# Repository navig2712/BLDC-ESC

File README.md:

# BLDC-ESC
All the files necessary files include  code for  DIY BLDC ESC
ESC V0----PCB files
Protues---Simulation files
Code

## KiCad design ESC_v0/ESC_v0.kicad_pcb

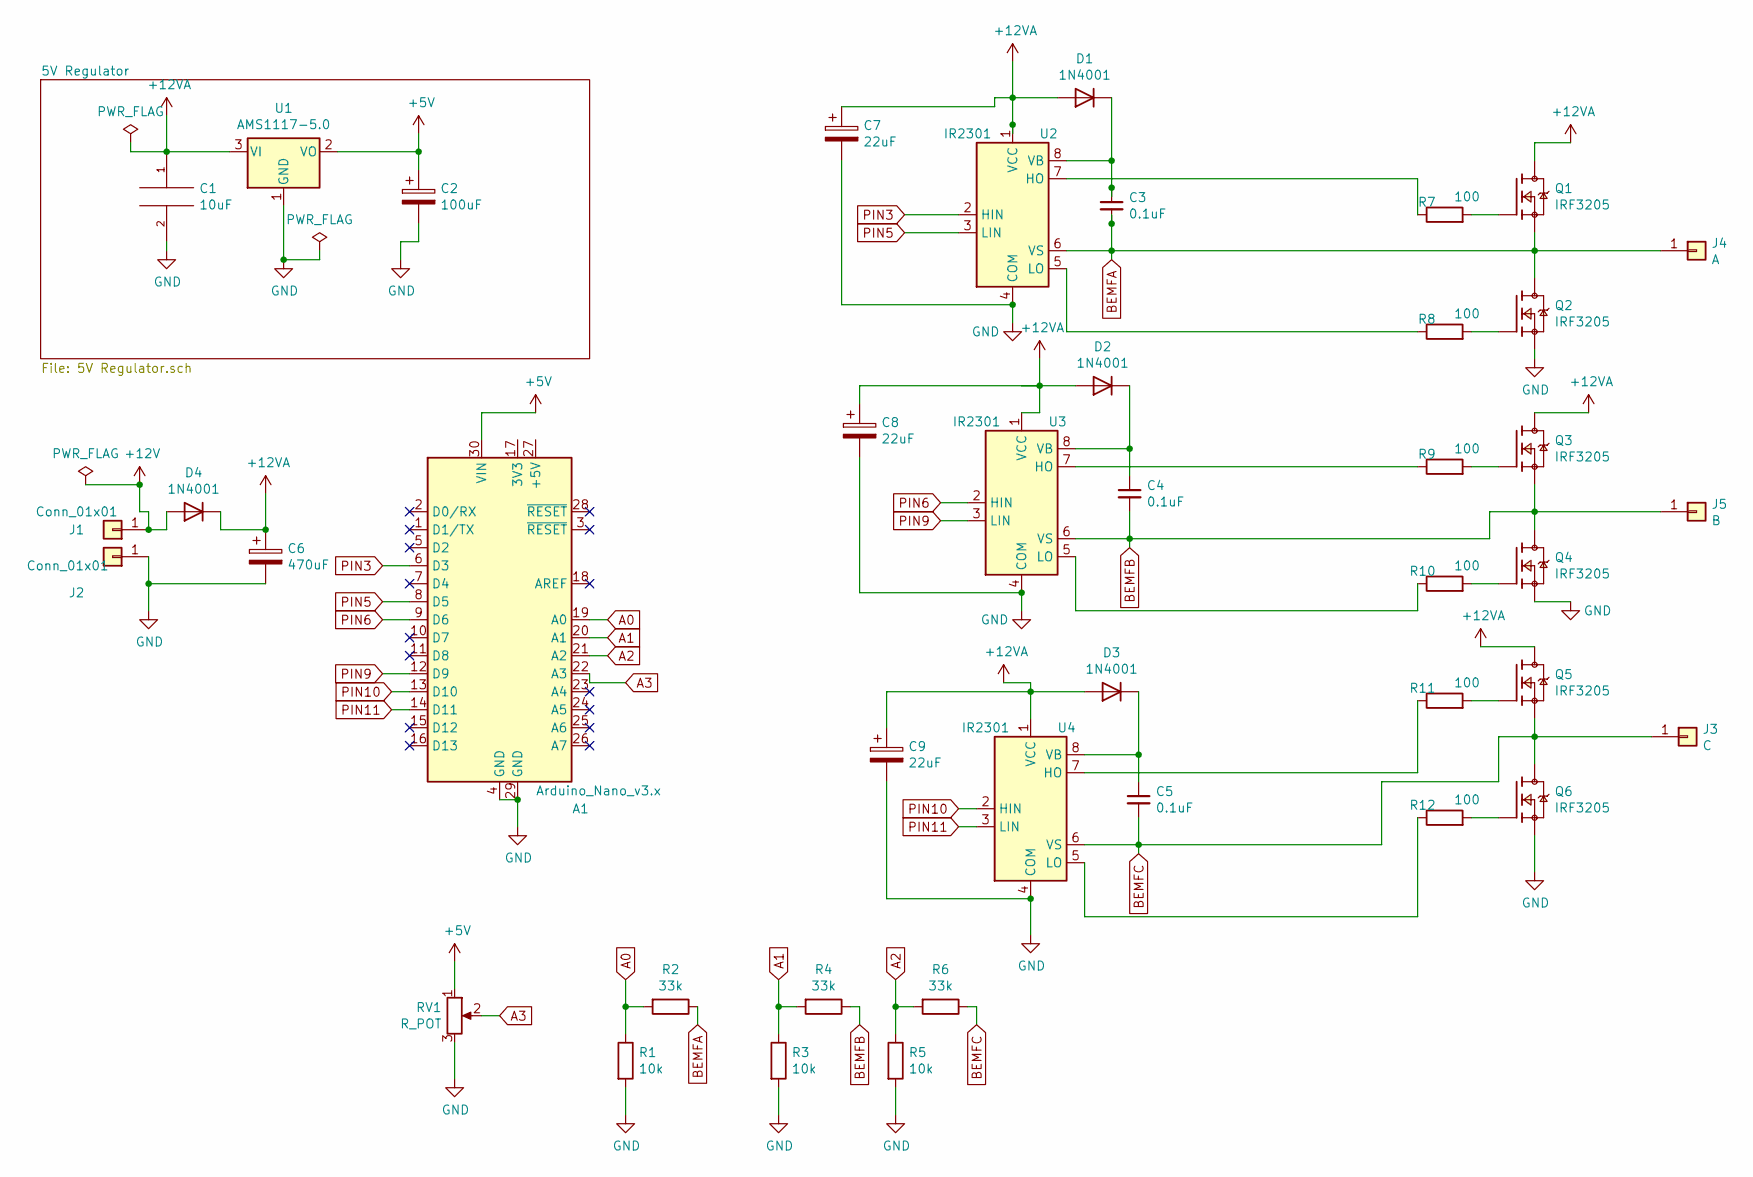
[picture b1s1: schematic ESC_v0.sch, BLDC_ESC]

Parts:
A1: Arduino_Nano_v3.x; Arduino_Nano
C1: 10uF; C_Disc_D7.0mm_W2.5mm_P5.00mm
C2: 100uF; CP_Radial_D8.0mm_P3.80mm
C3, C4, C5: 0.1uF; C_Disc_D5.0mm_W2.5mm_P2.50mm
C6: 470uF; CP_Radial_D12.5mm_P5.00mm
C7, C8, C9: 22uF; CP_Radial_D5.0mm_P2.00mm
D1, D2, D3, D4: 1N4001; D_DO-41_SOD81_P10.16mm_Horizontal
J1, J2: Conn_01x01; TestPoint_Pad_3.0x3.0mm
J3: C; TestPoint_Pad_4.0x4.0mm
J4: A; TestPoint_Pad_4.0x4.0mm
J5: B; TestPoint_Pad_4.0x4.0mm
Q1, Q2, Q3, Q4, Q5, Q6: IRF3205; TO254P1041X444X2933-3; PARTREV 01/25/01
R1, R3, R5: 10k; R_Axial_DIN0207_L6.3mm_D2.5mm_P7.62mm_Horizontal
R2, R4, R6: 33k; R_Axial_DIN0207_L6.3mm_D2.5mm_P7.62mm_Horizontal
R7, R8, R9, R10, R11, R12: 100; R_Axial_DIN0207_L6.3mm_D2.5mm_P7.62mm_Horizontal
RV1: R_POT; Potentiometer_Alps_RK163_Single_Horizontal
U1: AMS1117-5.0; SOT-223-3_TabPin2
U2, U3, U4: IR2301; DIP-8_W7.62mm

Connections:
+5V: A1.30 (VIN), C2.1, RV1.1, U1.2 (VO)
+12V: D4.2 (A), J1.1
+12VA: C1.1, C6.1, C7.1, C8.1, C9.1, D1.2 (A), D2.2 (A), D3.2 (A), D4.1 (K), Q1.2, Q3.2, Q5.2, U1.3 (VI), U2.1 (VCC), U3.1 (VCC), U4.1 (VCC)
A0: A1.19 (A0), R1.1, R2.2
A1: A1.20 (A1), R3.1, R4.2
A2: A1.21 (A2), R5.1, R6.2
A3: A1.22 (A3), RV1.2
BEMFA: C3.2, J4.1, Q1.3, Q2.2, R2.1, U2.6 (VS)
BEMFB: C4.2, J5.1, Q3.3, Q4.2, R4.1, U3.6 (VS)
BEMFC: C5.2, J3.1, Q5.3, Q6.2, R6.1, U4.6 (VS)
GND: A1.4 (GND), A1.29 (GND), C1.2, C2.2, C6.2, C7.2, C8.2, C9.2, J2.1, Q2.3, Q4.3, Q6.3, R1.2, R3.2, R5.2, RV1.3, U1.1 (GND), U2.4 (COM), U3.4 (COM), U4.4 (COM)
unnamed: C3.1, D1.1 (K), U2.8 (VB)
unnamed: C4.1, D2.1 (K), U3.8 (VB)
unnamed: C5.1, D3.1 (K), U4.8 (VB)
unnamed: Q1.1, R7.2
unnamed: Q2.1, R8.2
unnamed: Q3.1, R9.2
unnamed: Q4.1, R10.2
unnamed: Q5.1, R11.2
unnamed: Q6.1, R12.2
unnamed: R7.1, U2.7 (HO)
unnamed: R8.1, U2.5 (LO)
unnamed: R9.1, U3.7 (HO)
unnamed: R10.1, U3.5 (LO)
unnamed: R11.1, U4.7 (HO)
unnamed: R12.1, U4.5 (LO)
PIN3: A1.6 (D3), U2.2 (HIN)
PIN5: A1.8 (D5), U2.3 (LIN)
PIN6: A1.9 (D6), U3.2 (HIN)
PIN9: A1.12 (D9), U3.3 (LIN)
PIN10: A1.13 (D10), U4.2 (HIN)
PIN11: A1.14 (D11), U4.3 (LIN)

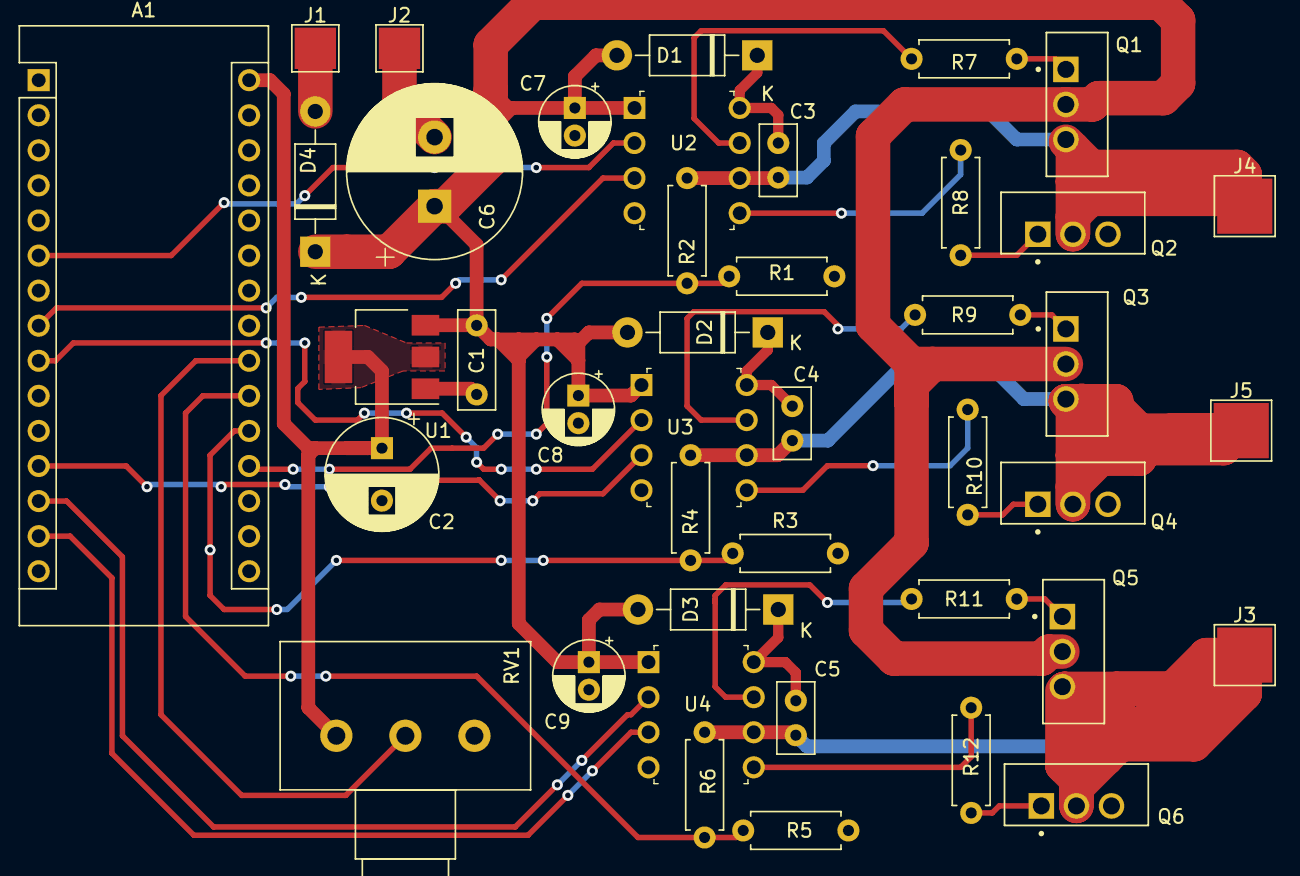
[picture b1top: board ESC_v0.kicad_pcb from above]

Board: 2 copper layers, 42 parts (0 on the bottom side), 32 nets.
